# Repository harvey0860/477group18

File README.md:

# 477group18
Harvey,Hank, Tony, Alan

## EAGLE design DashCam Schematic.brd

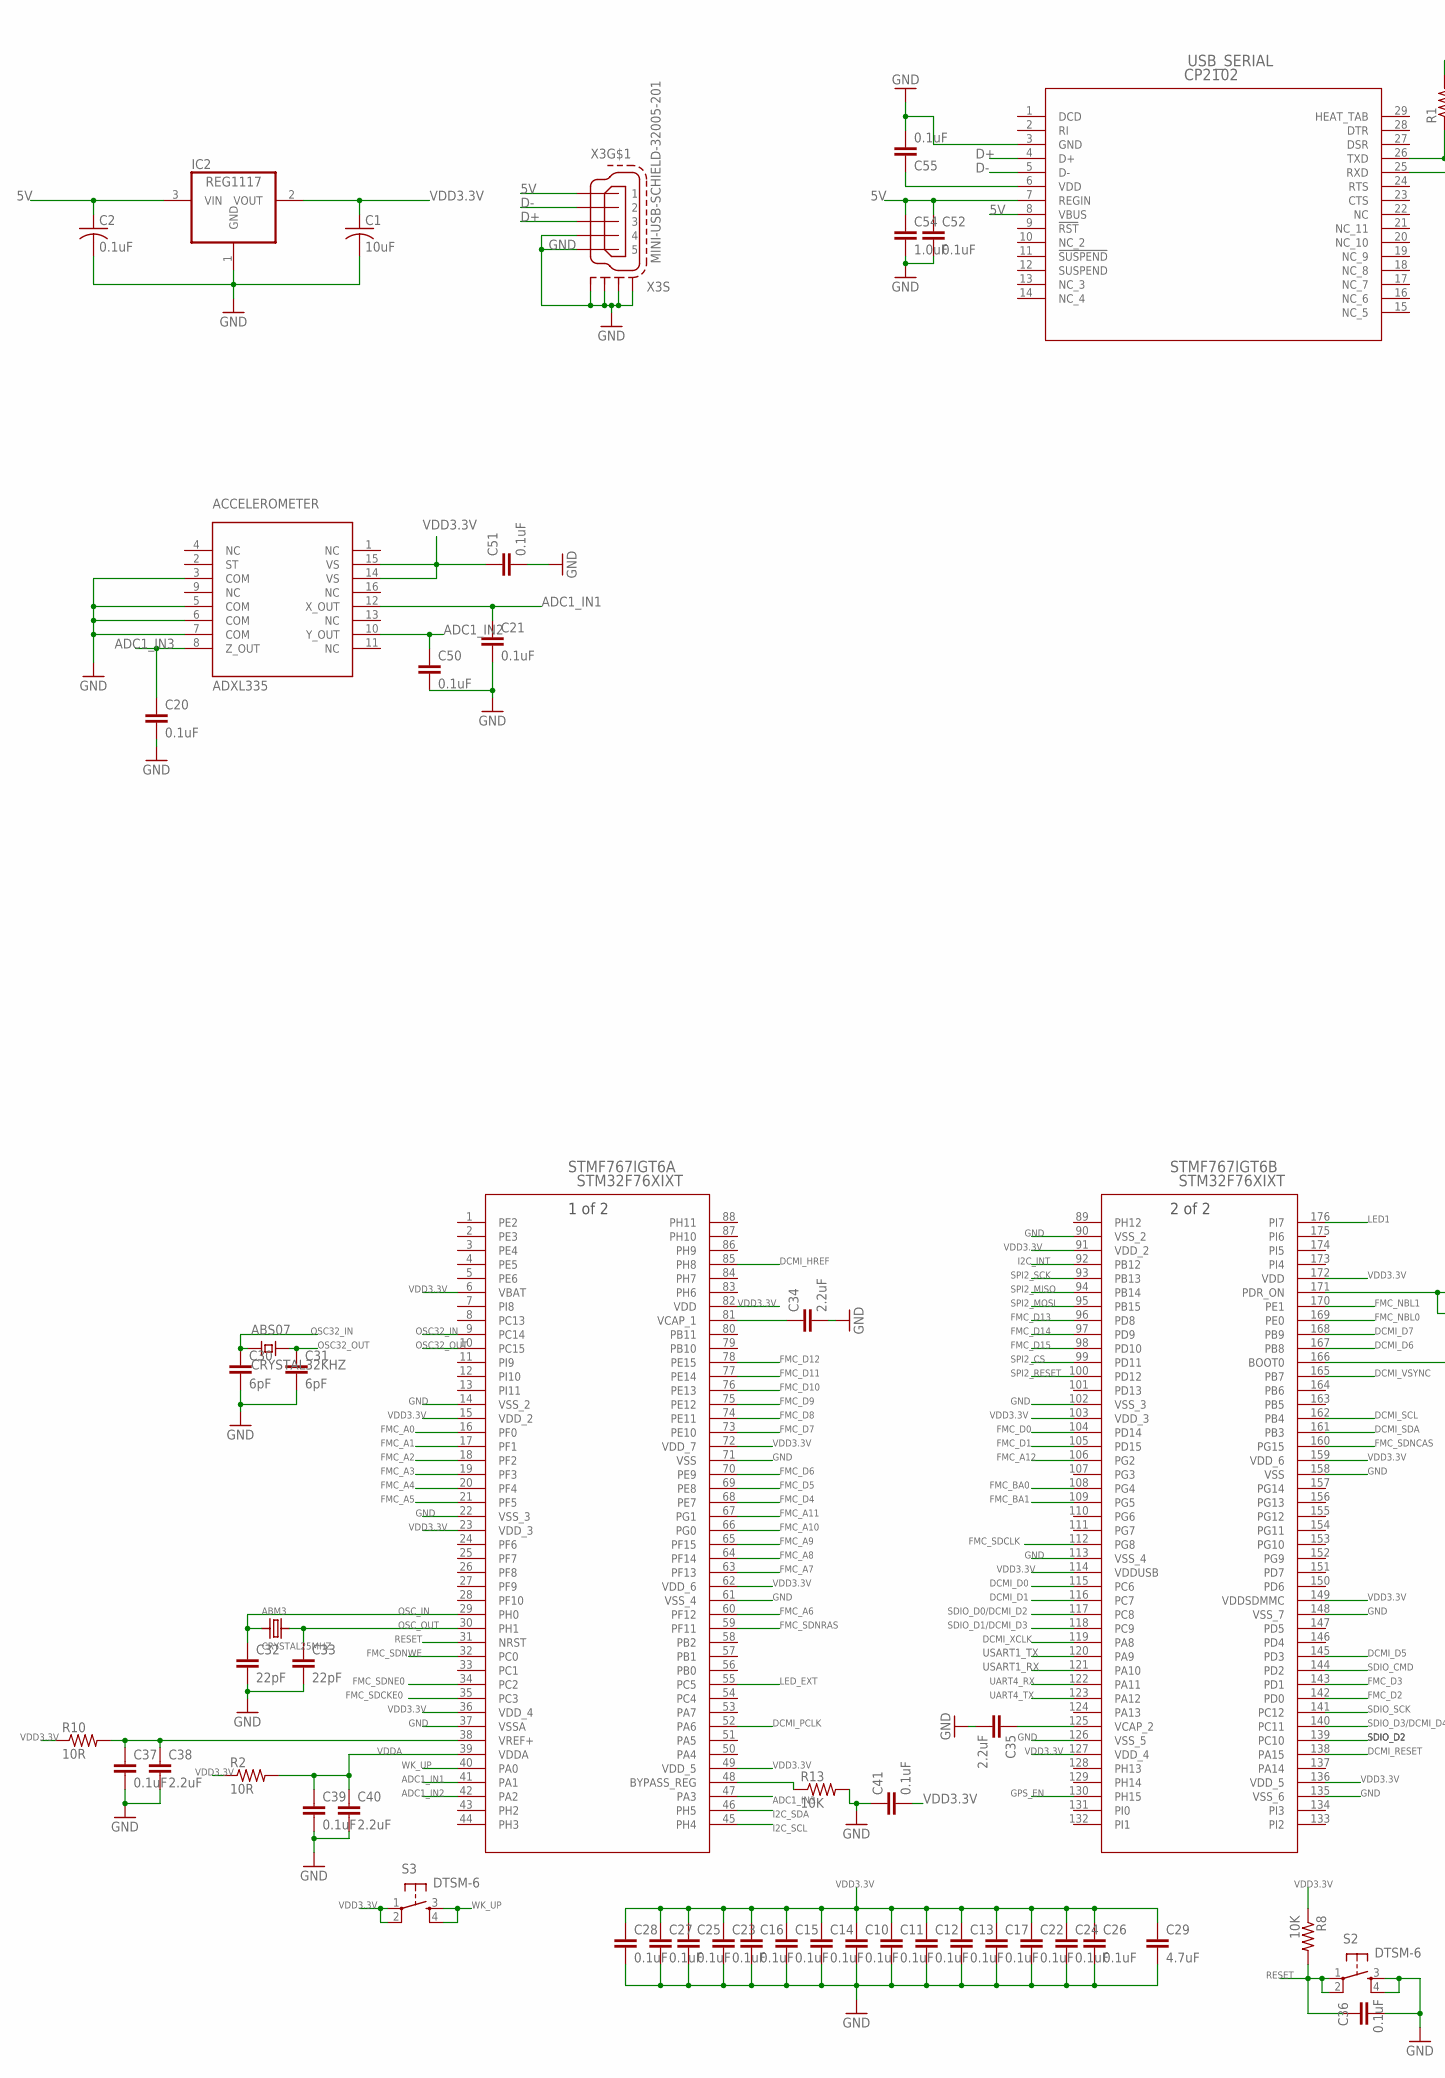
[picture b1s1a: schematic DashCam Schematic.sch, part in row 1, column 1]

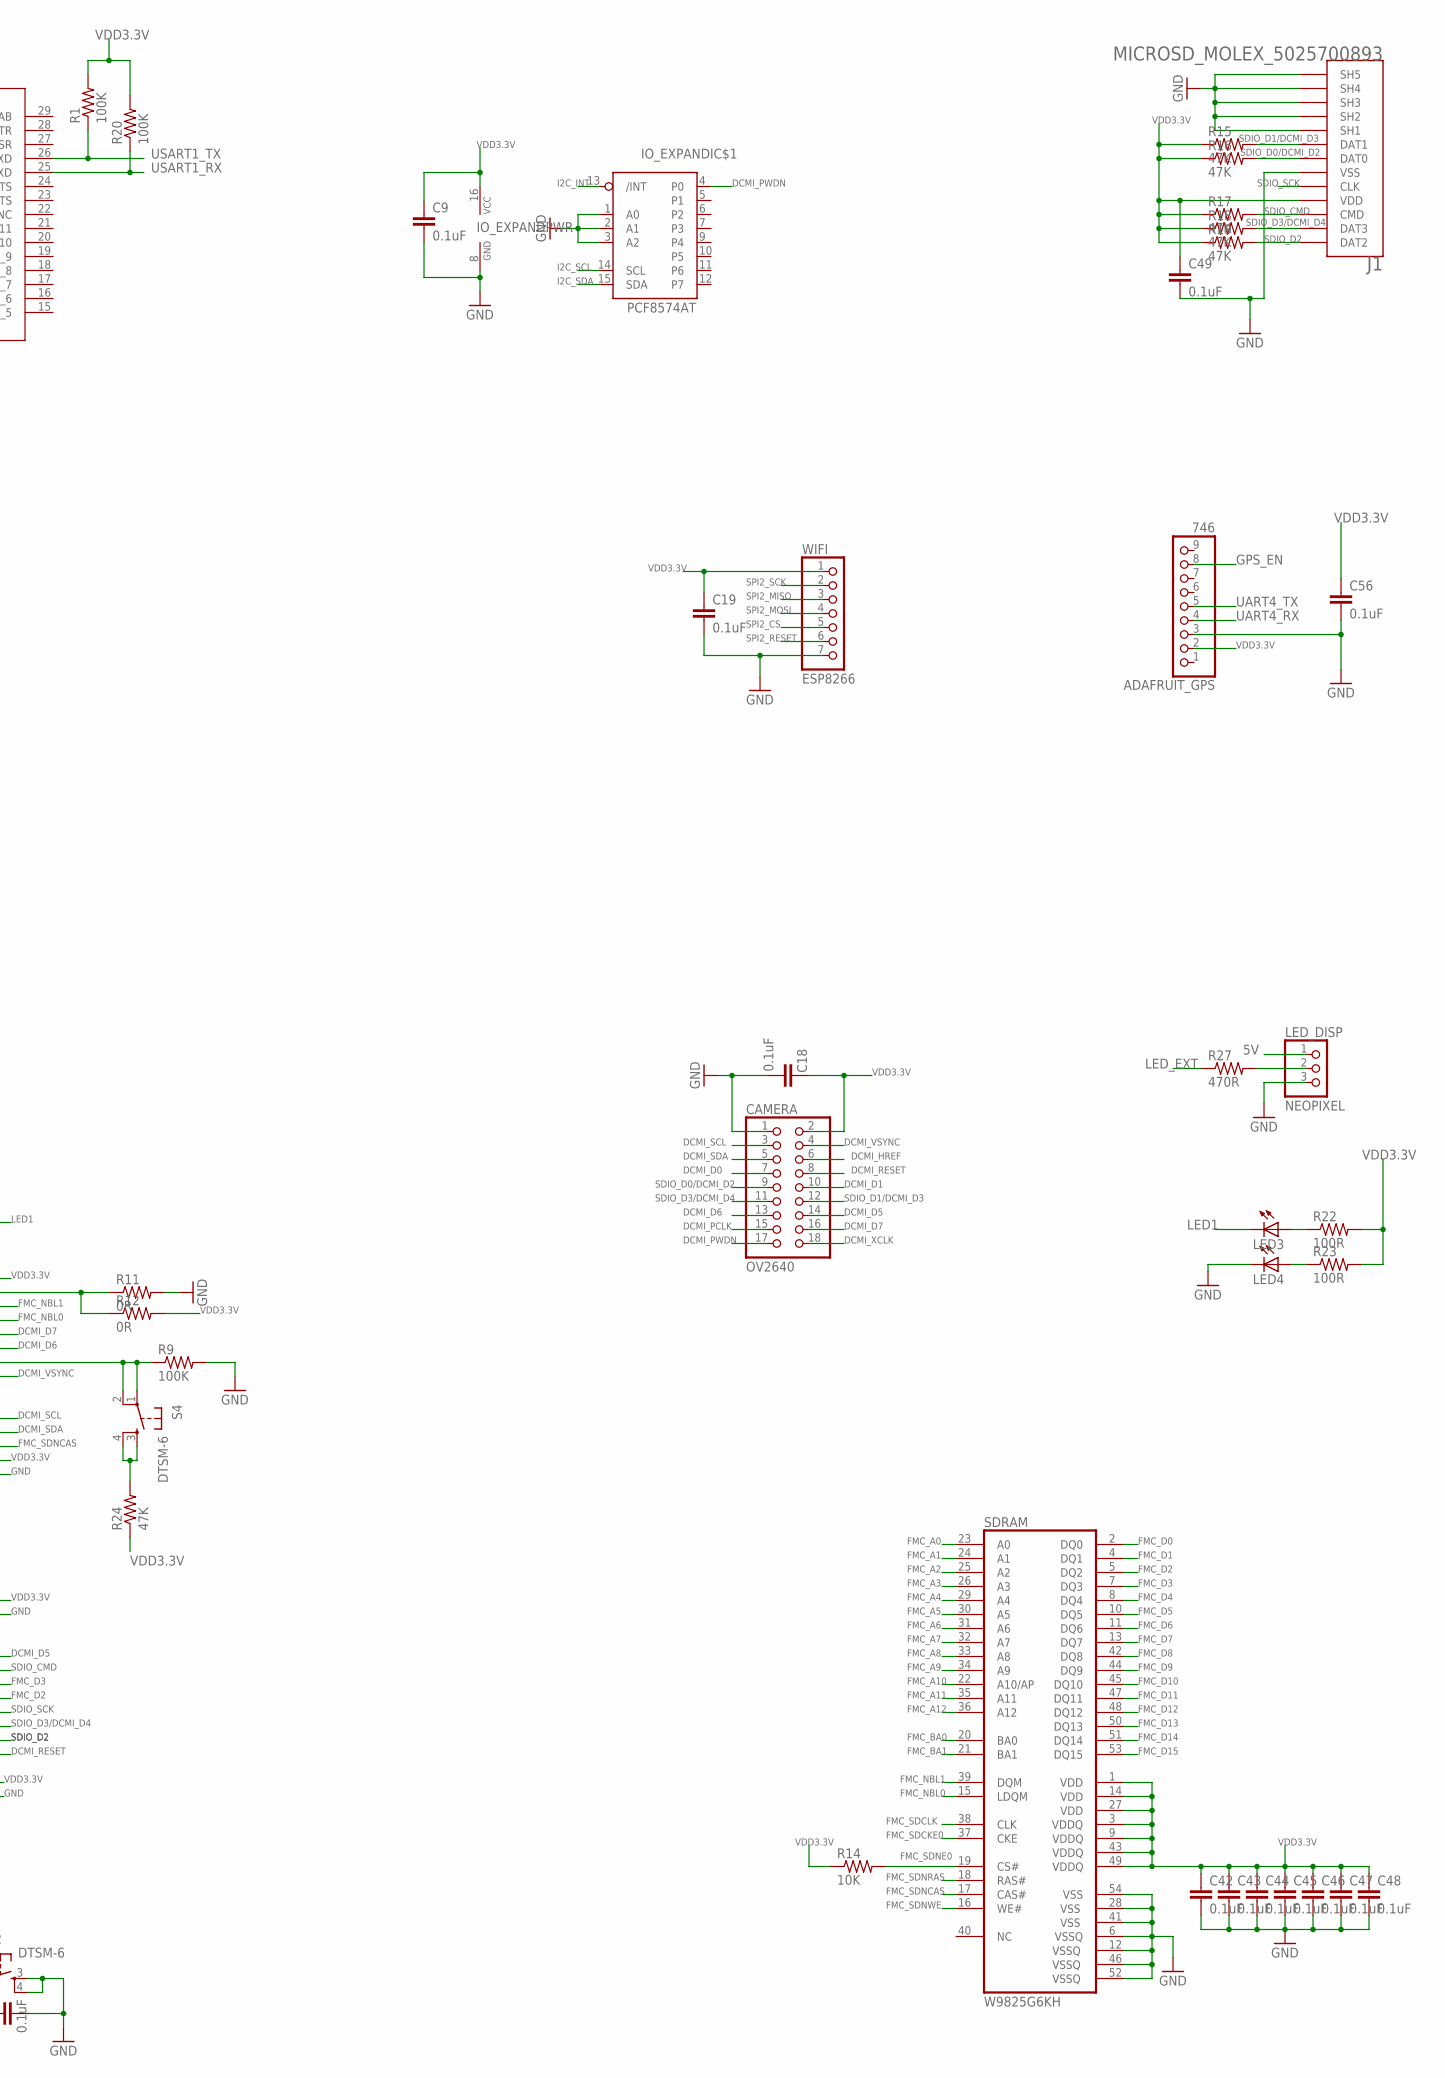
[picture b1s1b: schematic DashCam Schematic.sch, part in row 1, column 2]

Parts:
ABM3: CRYSTAL25MHZ; 6X3.3MM
ABS07: CRYSTAL32KHZ; 2-SMD_ABM7
ACCELEROMETER: ADXL335; LFCSP16
ADAFRUIT_GPS: 746; 1X09
C1: 10uF; C0805
C2, C9, C10, C11, C12, C13, C14, C15, C16, C17, C18, C19, C20, C21, C22, C23, C24, C25, C26, C27, C28, C36, C37, C39, C41, C42, C43, C44, C45, C46, C47, C48, C49, C50, C51, C52, C55, C56: 0.1uF; C0402
C29: 4.7uF; C0603
C30, C31: 6pF; C0402
C32, C33: 22pF; C0201
C34, C35, C38, C40: 2.2uF; C0805
C54: 1.0uF; C0402
CAMERA: OV2640; 2X09/90
IC2: REG1117; SOT223
IO_EXPAND: PCF8574AT; SO16
J1: MICROSD_MOLEX_5025700893; 5025700893
LED3, LED4: LEDCHIP-LED0603; CHIP-LED0603
LED_DISP: NEOPIXEL; 1X03
R1, R9, R20: 100K; R0805
R2, R10: 10R; R0603
R8, R13, R14: 10K; R0402
R11, R12: 0R; R0402
R15, R16, R17, R18, R19, R24: 47K; R0402
R22, R23: 100R; R0402
R27: 470R; R0603
S2, S3, S4: DTSM-6
SDRAM: W9825G6KH; TSOP54
STMF767IGT6: STM32F76XIXT; LQFP-176_24X24
USB_SERIAL: CP2102; QFN28N5X5-0P5P
WIFI: ESP8266; 1X07
X3: MINI-USB-SCHIELD-32005-201; 32005-201

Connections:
5V: C2.1, C52.1, C54.1, IC2.3 (VIN), LED_DISP.1, USB_SERIAL.7 (REGIN), USB_SERIAL.8 (VBUS), X3.1
ADC1_IN1: ACCELEROMETER.12 (X_OUT), C21.1, STMF767IGT6.41 (PA1)
ADC1_IN2: ACCELEROMETER.10 (Y_OUT), C50.1, STMF767IGT6.42 (PA2)
ADC1_IN3: ACCELEROMETER.8 (Z_OUT), C20.1, STMF767IGT6.47 (PA3)
D+: USB_SERIAL.4 (D+), X3.3
D-: USB_SERIAL.5 (D-), X3.2
DCMI_D0: CAMERA.7, STMF767IGT6.115 (PC6)
DCMI_D1: CAMERA.10, STMF767IGT6.116 (PC7)
DCMI_D5: CAMERA.14, STMF767IGT6.145 (PD3)
DCMI_D6: CAMERA.13, STMF767IGT6.167 (PB8)
DCMI_D7: CAMERA.16, STMF767IGT6.168 (PB9)
DCMI_HREF: CAMERA.6, STMF767IGT6.85 (PH8)
DCMI_PCLK: CAMERA.15, STMF767IGT6.52 (PA6)
DCMI_PWDN: CAMERA.17, IO_EXPAND.4 (P0)
DCMI_RESET: CAMERA.8, STMF767IGT6.138 (PA15)
DCMI_SCL: CAMERA.3, STMF767IGT6.162 (PB4)
DCMI_SDA: CAMERA.5, STMF767IGT6.161 (PB3)
DCMI_VSYNC: CAMERA.4, STMF767IGT6.165 (PB7)
DCMI_XCLK: CAMERA.18, STMF767IGT6.119 (PA8)
FMC_A0: SDRAM.23 (A0), STMF767IGT6.16 (PF0)
FMC_A1: SDRAM.24 (A1), STMF767IGT6.17 (PF1)
FMC_A2: SDRAM.25 (A2), STMF767IGT6.18 (PF2)
FMC_A3: SDRAM.26 (A3), STMF767IGT6.19 (PF3)
FMC_A4: SDRAM.29 (A4), STMF767IGT6.20 (PF4)
FMC_A5: SDRAM.30 (A5), STMF767IGT6.21 (PF5)
FMC_A6: SDRAM.31 (A6), STMF767IGT6.60 (PF12)
FMC_A7: SDRAM.32 (A7), STMF767IGT6.63 (PF13)
FMC_A8: SDRAM.33 (A8), STMF767IGT6.64 (PF14)
FMC_A9: SDRAM.34 (A9), STMF767IGT6.65 (PF15)
FMC_A10: SDRAM.22 (A10/AP), STMF767IGT6.66 (PG0)
FMC_A11: SDRAM.35 (A11), STMF767IGT6.67 (PG1)
FMC_A12: SDRAM.36 (A12), STMF767IGT6.106 (PG2)
FMC_BA0: SDRAM.20 (BA0), STMF767IGT6.108 (PG4)
FMC_BA1: SDRAM.21 (BA1), STMF767IGT6.109 (PG5)
FMC_D0: SDRAM.2 (DQ0), STMF767IGT6.104 (PD14)
FMC_D1: SDRAM.4 (DQ1), STMF767IGT6.105 (PD15)
FMC_D2: SDRAM.5 (DQ2), STMF767IGT6.142 (PD0)
FMC_D3: SDRAM.7 (DQ3), STMF767IGT6.143 (PD1)
FMC_D4: SDRAM.8 (DQ4), STMF767IGT6.68 (PE7)
FMC_D5: SDRAM.10 (DQ5), STMF767IGT6.69 (PE8)
FMC_D6: SDRAM.11 (DQ6), STMF767IGT6.70 (PE9)
FMC_D7: SDRAM.13 (DQ7), STMF767IGT6.73 (PE10)
FMC_D8: SDRAM.42 (DQ8), STMF767IGT6.74 (PE11)
FMC_D9: SDRAM.44 (DQ9), STMF767IGT6.75 (PE12)
FMC_D10: SDRAM.45 (DQ10), STMF767IGT6.76 (PE13)
FMC_D11: SDRAM.47 (DQ11), STMF767IGT6.77 (PE14)
FMC_D12: SDRAM.48 (DQ12), STMF767IGT6.78 (PE15)
FMC_D13: SDRAM.50 (DQ13), STMF767IGT6.96 (PD8)
FMC_D14: SDRAM.51 (DQ14), STMF767IGT6.97 (PD9)
FMC_D15: SDRAM.53 (DQ15), STMF767IGT6.98 (PD10)
FMC_NBL0: SDRAM.15 (LDQM), STMF767IGT6.169 (PE0)
FMC_NBL1: SDRAM.39 (DQM), STMF767IGT6.170 (PE1)
FMC_SDCKE0: SDRAM.37 (CKE), STMF767IGT6.35 (PC3)
FMC_SDCLK: SDRAM.38 (CLK), STMF767IGT6.112 (PG8)
FMC_SDNCAS: SDRAM.17 (CAS#), STMF767IGT6.160 (PG15)
FMC_SDNE0: R14.2, SDRAM.19 (CS#), STMF767IGT6.34 (PC2)
FMC_SDNRAS: SDRAM.18 (RAS#), STMF767IGT6.59 (PF11)
FMC_SDNWE: SDRAM.16 (WE#), STMF767IGT6.32 (PC0)
GND: ACCELEROMETER.3 (COM), ACCELEROMETER.5 (COM), ACCELEROMETER.6 (COM), ACCELEROMETER.7 (COM), ADAFRUIT_GPS.3, C1.2, C2.2, C9.2, C10.2, C11.2, C12.2, C13.2, C14.2, C15.2, C16.2, C17.2, C18.2, C19.2, C20.2, C21.2, C22.2, C23.2, C24.2, C25.2, C26.2, C27.2, C28.2, C29.2, C30.2, C31.2, C32.2, C33.2, C34.2, C35.2, C36.2, C37.2, C38.2, C39.2, C40.2, C41.1, C42.2, C43.2, C44.2, C45.2, C46.2, C47.2, C48.2, C49.2, C50.2, C51.2, C52.2, C54.2, C55.2, C56.2, CAMERA.1, IC2.1 (GND), IO_EXPAND.1 (A0), IO_EXPAND.2 (A1), IO_EXPAND.3 (A2), IO_EXPAND.8 (GND), J1.GND0 (SH1), J1.GND1 (SH2), J1.GND2 (SH3), J1.GND3 (SH4), J1.GND4 (SH5), J1.P$6 (VSS), LED4.C, LED_DISP.3, R9.2, R11.2, R13.2, S2.3, S2.4, SDRAM.6 (VSSQ), SDRAM.12 (VSSQ), SDRAM.28 (VSS), SDRAM.41 (VSS), SDRAM.46 (VSSQ), SDRAM.52 (VSSQ), SDRAM.54 (VSS), STMF767IGT6.14 (VSS_2), STMF767IGT6.22 (VSS_3), STMF767IGT6.37 (VSSA), STMF767IGT6.61 (VSS_4), STMF767IGT6.71 (VSS), STMF767IGT6.90 (VSS_2), STMF767IGT6.102 (VSS_3), STMF767IGT6.113 (VSS_4), STMF767IGT6.126 (VSS_5), STMF767IGT6.135 (VSS_6), STMF767IGT6.148 (VSS_7), STMF767IGT6.158 (VSS), USB_SERIAL.3 (GND), WIFI.7, X3.4, X3.5, X3.M1 (S1), X3.M2 (S2), X3.M3 (S3), X3.M4 (S4)
GPS_EN: ADAFRUIT_GPS.8, STMF767IGT6.130 (PH15)
I2C_INT: IO_EXPAND.13 (/INT), STMF767IGT6.92 (PB12)
I2C_SCL: IO_EXPAND.14 (SCL), STMF767IGT6.45 (PH4)
I2C_SDA: IO_EXPAND.15 (SDA), STMF767IGT6.46 (PH5)
LED1: LED3.C, STMF767IGT6.176 (PI7)
LED_EXT: R27.1, STMF767IGT6.55 (PC5)
unnamed: R13.1, STMF767IGT6.48 (BYPASS_REG)
unnamed: R9.1, S4.1, S4.2, STMF767IGT6.166 (BOOT0)
unnamed: C55.1, USB_SERIAL.6 (VDD)
unnamed: LED3.A, R22.1
unnamed: C34.1, STMF767IGT6.81 (VCAP_1)
unnamed: C35.1, STMF767IGT6.125 (VCAP_2)
unnamed: R11.1, R12.1, STMF767IGT6.171 (PDR_ON)
unnamed: LED4.A, R23.1
unnamed: R24.2, S4.3, S4.4
unnamed: LED_DISP.2, R27.2
unnamed: C37.1, C38.1, R10.2, STMF767IGT6.38 (VREF+)
OSC32_IN: ABS07.P$1, C30.1, STMF767IGT6.9 (PC14)
OSC32_OUT: ABS07.P$2, C31.1, STMF767IGT6.10 (PC15)
OSC_IN: ABM3.1, C32.1, STMF767IGT6.29 (PH0)
OSC_OUT: ABM3.2, C33.1, STMF767IGT6.30 (PH1)
RESET: C36.1, R8.2, S2.1, S2.2, STMF767IGT6.31 (NRST)
SDIO_CMD: J1.P$3 (CMD), R17.2, STMF767IGT6.144 (PD2)
SDIO_D0/DCMI_D2: CAMERA.9, J1.P$7 (DAT0), R16.2, STMF767IGT6.117 (PC8)
SDIO_D1/DCMI_D3: CAMERA.12, J1.P$8 (DAT1), R15.2, STMF767IGT6.118 (PC9)
SDIO_D2: J1.P$1 (DAT2), R19.2, STMF767IGT6.139 (PC10)
SDIO_D3/DCMI_D4: CAMERA.11, J1.P$2 (DAT3), R18.2, STMF767IGT6.140 (PC11)
SDIO_SCK: J1.P$5 (CLK), STMF767IGT6.141 (PC12)
SPI2_CS: STMF767IGT6.99 (PD11), WIFI.5
SPI2_MISO: STMF767IGT6.94 (PB14), WIFI.3
SPI2_MOSI: STMF767IGT6.95 (PB15), WIFI.4
SPI2_RESET: STMF767IGT6.100 (PD12), WIFI.6
SPI2_SCK: STMF767IGT6.93 (PB13), WIFI.2
UART4_RX: ADAFRUIT_GPS.4, STMF767IGT6.122 (PA11)
UART4_TX: ADAFRUIT_GPS.5, STMF767IGT6.123 (PA12)
USART1_RX: R20.1, STMF767IGT6.121 (PA10), USB_SERIAL.25 (RXD)
USART1_TX: R1.1, STMF767IGT6.120 (PA9), USB_SERIAL.26 (TXD)
VDD3.3V: ACCELEROMETER.14 (VS), ACCELEROMETER.15 (VS), ADAFRUIT_GPS.2, C1.1, C9.1, C10.1, C11.1, C12.1, C13.1, C14.1, C15.1, C16.1, C17.1, C18.1, C19.1, C22.1, C23.1, C24.1, C25.1, C26.1, C27.1, C28.1, C29.1, C41.2, C42.1, C43.1, C44.1, C45.1, C46.1, C47.1, C48.1, C49.1, C51.1, C56.1, CAMERA.2, IC2.2 (VOUT), IO_EXPAND.16 (VCC), J1.P$4 (VDD), R1.2, R2.1, R8.1, R10.1, R12.2, R14.1, R15.1, R16.1, R17.1, R18.1, R19.1, R20.2, R22.2, R23.2, R24.1, S3.1, S3.2, SDRAM.1 (VDD), SDRAM.3 (VDDQ), SDRAM.9 (VDDQ), SDRAM.14 (VDD), SDRAM.27 (VDD), SDRAM.43 (VDDQ), SDRAM.49 (VDDQ), STMF767IGT6.6 (VBAT), STMF767IGT6.15 (VDD_2), STMF767IGT6.23 (VDD_3), STMF767IGT6.36 (VDD_4), STMF767IGT6.49 (VDD_5), STMF767IGT6.62 (VDD_6), STMF767IGT6.72 (VDD_7), STMF767IGT6.82 (VDD), STMF767IGT6.91 (VDD_2), STMF767IGT6.103 (VDD_3), STMF767IGT6.114 (VDDUSB), STMF767IGT6.127 (VDD_4), STMF767IGT6.136 (VDD_5), STMF767IGT6.149 (VDDSDMMC), STMF767IGT6.159 (VDD_6), STMF767IGT6.172 (VDD), WIFI.1
VDDA: C39.1, C40.1, R2.2, STMF767IGT6.39 (VDDA)
WK_UP: S3.3, S3.4, STMF767IGT6.40 (PA0)

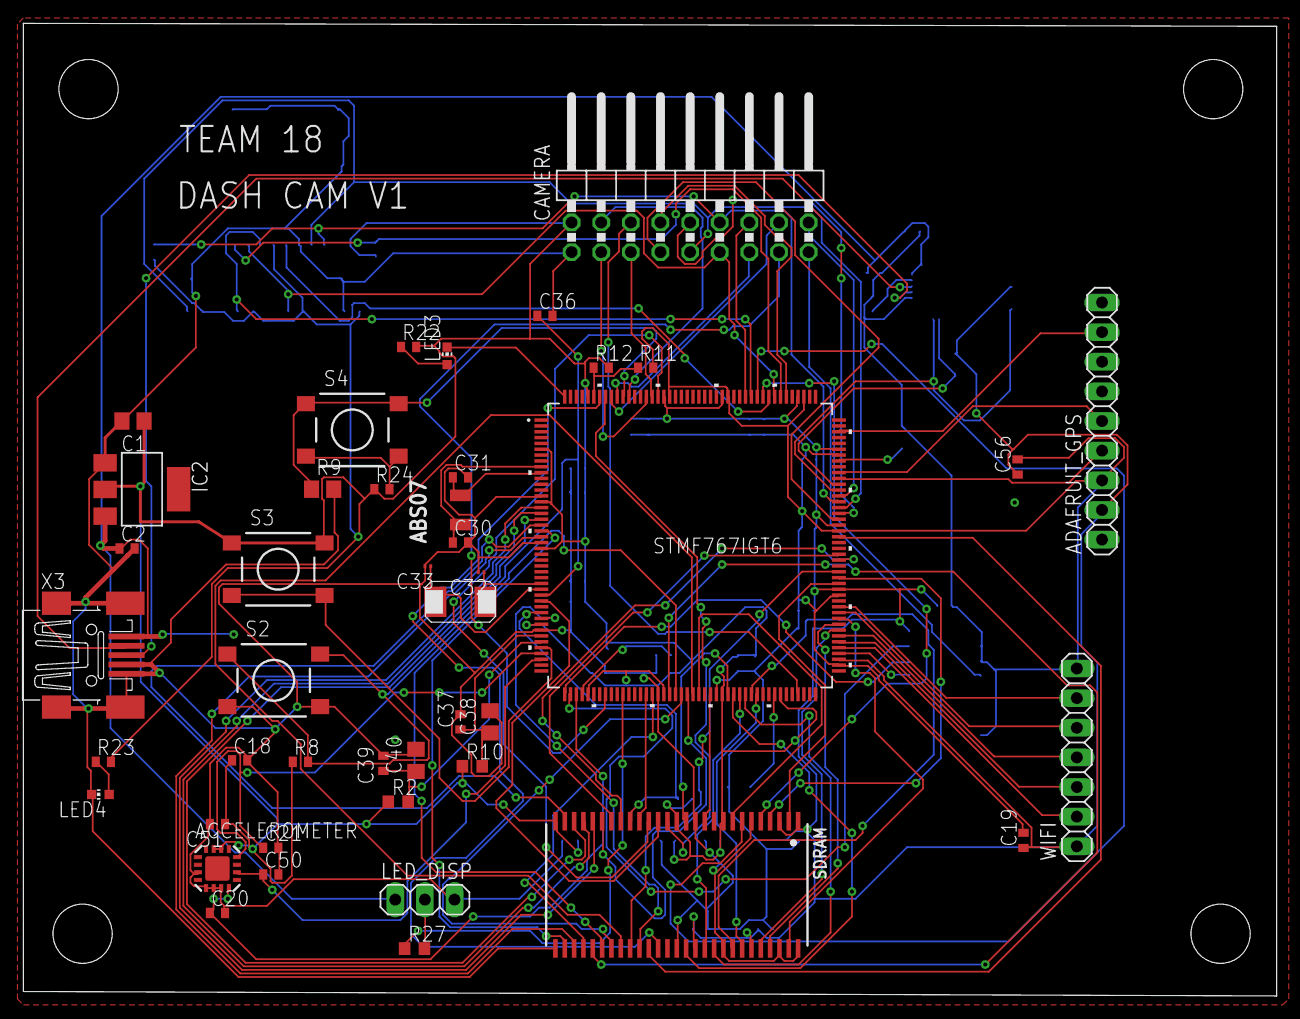
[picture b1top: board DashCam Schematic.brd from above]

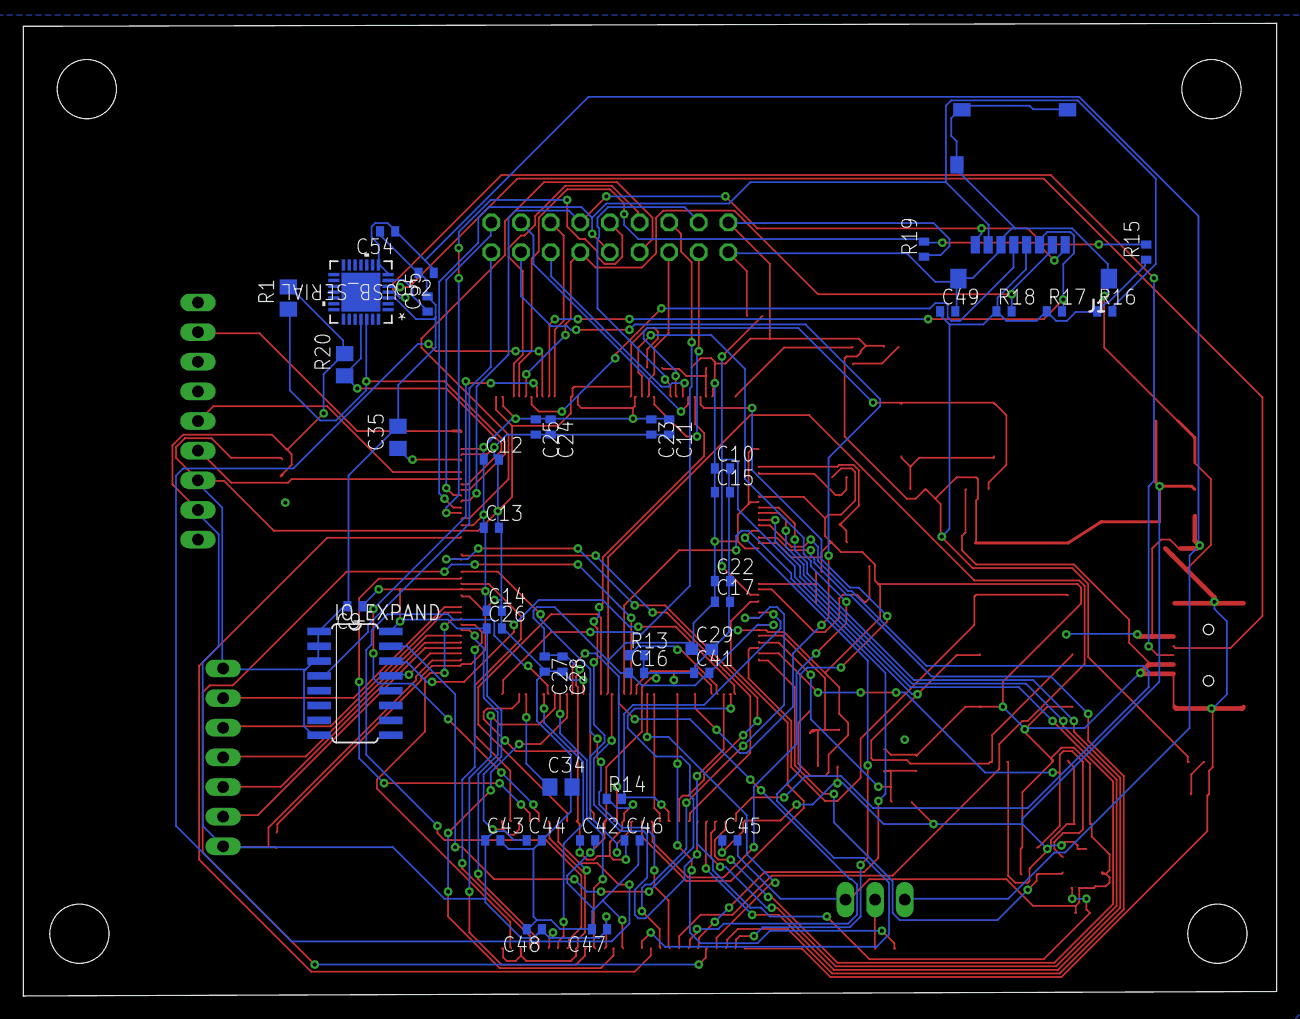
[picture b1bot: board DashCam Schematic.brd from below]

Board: 2 copper layers, 107.4 x 83.4 mm, 87 parts (43 on the bottom side), 99 nets.
